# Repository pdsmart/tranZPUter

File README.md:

## Foreword

The tranZPUter is actively being developed and will be reflected in this document.

## Overview

The Sharp MZ80A is based on the Z80 CPU running at 2MHz. It is vintage and under powered compared with modern computers (or a Raspberry Pi). Besides being part of history, it has a software base that is useful from time to time and still has followers. A software Emulator could be written to prolong the usage of the software but there is something special about using original hardware and this is an alternative to keep the machine original yet provide an upgrade that can power the machine with multiple different CPU's (in FPGA, ie. ZPU, 68000 etc) and also power it with a Z80 running upto 128MHz. This is done by bus mastering where the original CPU is tri-stated and the FPGA takes control of the bus.

Besides providing more powerful and alternative CPU's and memory, the FPGA can also act as a Floppy Drive, Hard Drive etc using the connected SD Card and provide a menu system by overlaying the video memory when invoked.

This design is still a work in progress, I stopped development when I needed to advance the ZPU Evo SDRAM controller which I had been putting off for a while. The SDRAM is critical as the Cyclone 10LP on the CYC1000 has limited BRAM, only enough for the cache and IOCP Bootloader. Many features have been tested and the schematic/pcb made, it is just a matter of furthering the VHDL now that the SDRAM controller works and to develop the C/C++ code to provide the menu/SD services (already done in the ZPU code base).

I chose the CYC1000 as the FPGA solution as I am not competent soldering BGA devices, also at US$30 it is quite a cost effective choice. For software minded people, it is not that difficult to use a Pi Zero W or similar in place of the CYC1000 just a reworking of the PCB and interface logic, but that is a project for another time.

As the design replaces a Z80 in-situ it is not limited to the MZ80A but can be used in any Z80 based computer with the right software.

## tranZPUter

The tranZPUter gets its name from: A TRANsformable ZPU compuTER as the base CPU in the FPGA will be the ZPU Evo. The ZPU Evo will provide the Menu, SD, Video Overlay services to the Sharp MZ80A by tri-stating the original Z80 and accessing the MZ80A memory and peripherals as though they were ZPU devices.

To provide different CPU's it is just a matter of mapping in VHDL the softcore CPU signals to the MZ80A bus via this designs interface. The program memory could either be that on the MZ80A or the faster SDRAM. ie. There is no real need to use the MZ80A memory when using a softcore CPU. In my SharpMZ Emulator I run a Z80 at 112MHz using FPGA BRAM but tests show at least 128MHz is sustainable, thus a softcore Z80 CPU running at 128MHz with 48K BRAM slowing down only for MZ80A peripheral access would see a 64x boost in program run, which for say CP/M or database use is very desirable.

In the gallery are pictures of the current design and files uploaded onto github are relatively stable, WIP files wont be uploaded as they are in constant flux.

### Hardware

The basics of this design lie in Z80 bus mastering, ie. the ability to switch the Z80 out of circuit and control the computer as required. Bus mastering was typically used by devices such as DMA for fast transfer of data from an I/O device to memory, or memory to memory 
for applications such as video/graphics. The device taking control of the Z80 bus could transfer data much faster than the Z80 running a program, hence the benefit.

In this design, the bus mastering is used in a similar vein, taking control of the Z80 bus to transfer data between main memory and an SD Card or between the I/O processor and the Video display buffer for presentation of menu's. It is also used where a soft processor
completely idle's the hard Z80 and acts as the main computer CPU. ie. using a soft T-80 ZPU CPU, it can process applications at 128MHz in local memory and slow down to access I/O and the Video buffer on the host machine.

The design centres around lifting the original Z80 onto a daughter card and rerouting several of its signals such that they can be controlled as needed. The core of the design is an FPGA, the Altera Cyclone 10LP on a mini development board made by Trenz Electronics.
This could quite easily be a Raspberry Pi or Teensy 3.6 but the aim of this project is to design electronic hardware in an FPGA using VHDL and making use of the ZPU Processor I have been working on in a seperate project.

The choice of the Trenz Electronic development board put a number of restrictions on the design in so much as it only provides limited I/O facilities. There were not so many other choices of pre-built FPGA development boards with the same size and features to choose from
and designing an FPGA directly into the design from project onset was considered too much a risk because my experience with BGA (Ball Grid Array) packaging and soldering of them was almost zero (I have reballed existing chips but those were working designs!).

As there were limited I/O facilities, I had to make use of two 16bit tri-state buffer latches in an addressed mode rather than a 1:1 mode. ie. The Z80 Data, Address and Control lines eminating out of the FPGA have to be 'set' one word at a time, ie. write data to latch, write address
to latch, write control signals to latch etc. This slows down the speed at which the FPGA can control the Z80 host (to be honest, a 100MHz FPGA can run 50 operations and still match the 2MHz original bus speed) and complicates the logic by requirement of FSM's in VHDL.

It is further complicated by the fact that the signals controlling the latches have themselves to be written in an addressed mode rather than direct, again due to lack of I/O facilities on the FPGA board. Thus in the schematic above you can see IC U6 & U8 being written to via
the common 16bit data bus (shared with the latches) and clocked by a single output signal from the FPGA. A delay line is used such that a write to the latch is performed by signal CYC_CTL/RST going high, this reaches the latch ~8ns after the same signal connected to the Master Reset goes high, thus clocking in the
data. The latches are reset when CYC_CTL/RST goes low and this is enough to control the 16 bit latches U5 & U9. ie. to write a 16bit word into U5 the procedure would be:
```
CYC_CTL/RST low
Set CYC_D0:7 to 0x02 (ADDR_LE active, low)
Set CYC_CTL/RST high, data on CYC_D0:7 is latched into U6/U8 and ADDR_LE goes active enabling transfer of data on CYC_D0:15 into U5 registers (latches on the rising edge of ADDR_LE).
Set required data on CYC_D0:15 that will be passed across to the Z80 BUS.
Set CYC_CTL/RST low, ADDR_LE goes inactive (high) and the data on CYC_D0:15 is latched into U5
```

Once the FPGA FSM is fine tuned, the actual write and read to/from the Z80 bus will be transparent but it is overly complicated as mentioned due to lack of I/O on the Trenz development board. 

### To Do
1. Write the ZPU C/C++ code to take control of the MZ80A, save/update/restore the Video Memory (for Menu system), convert the Main/sharpmz.? Menu/control code, and additional glue to use the SD card.<br/>
2. Convert the T80 CPU to act as a Z80 upgrade for the MZ80A.

## Credits

Where I have used or based any component on a 3rd parties design I have included the original authors copyright notice. All 3rd party software, to my knowledge and research, is open source and freely useable, if there is found to be any component with licensing restrictions, it will be removed from this repository and a suitable link/config provided.

## Licenses

This design, hardware and software, is licensed under the GNU Public Licence v3.

### The Gnu Public License v3
 The source and binary files in this project marked as GPL v3 are free software: you can redistribute it and-or modify it under the terms of the GNU General Public License as published by the Free Software Foundation, either version 3 of the License, or (at your option) any later version.

 The source files are distributed in the hope that it will be useful, but WITHOUT ANY WARRANTY; without even the implied warranty of MERCHANTABILITY or FITNESS FOR A PARTICULAR PURPOSE.  See the GNU General Public License for more details.

 You should have received a copy of the GNU General Public License along with this program.  If not, see http://www.gnu.org/licenses/.

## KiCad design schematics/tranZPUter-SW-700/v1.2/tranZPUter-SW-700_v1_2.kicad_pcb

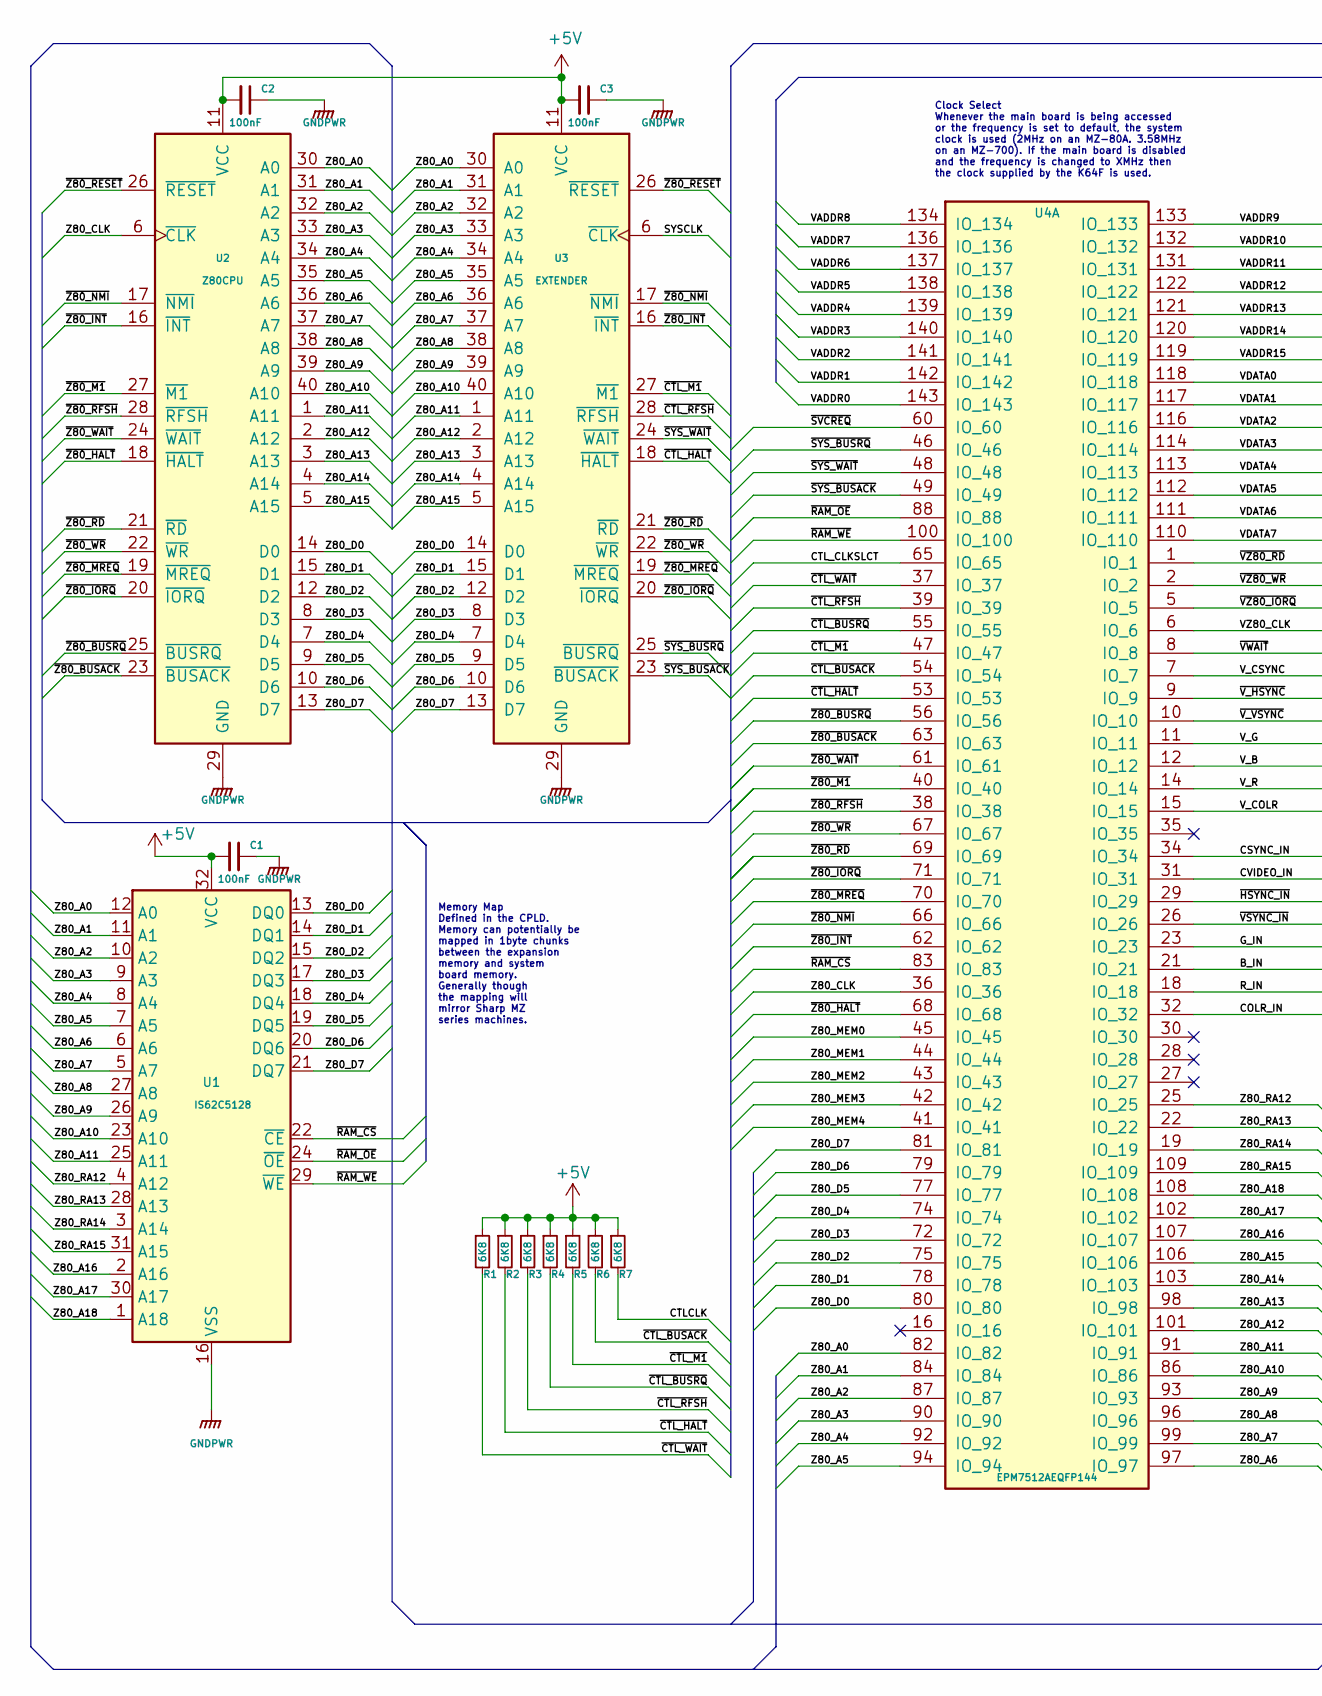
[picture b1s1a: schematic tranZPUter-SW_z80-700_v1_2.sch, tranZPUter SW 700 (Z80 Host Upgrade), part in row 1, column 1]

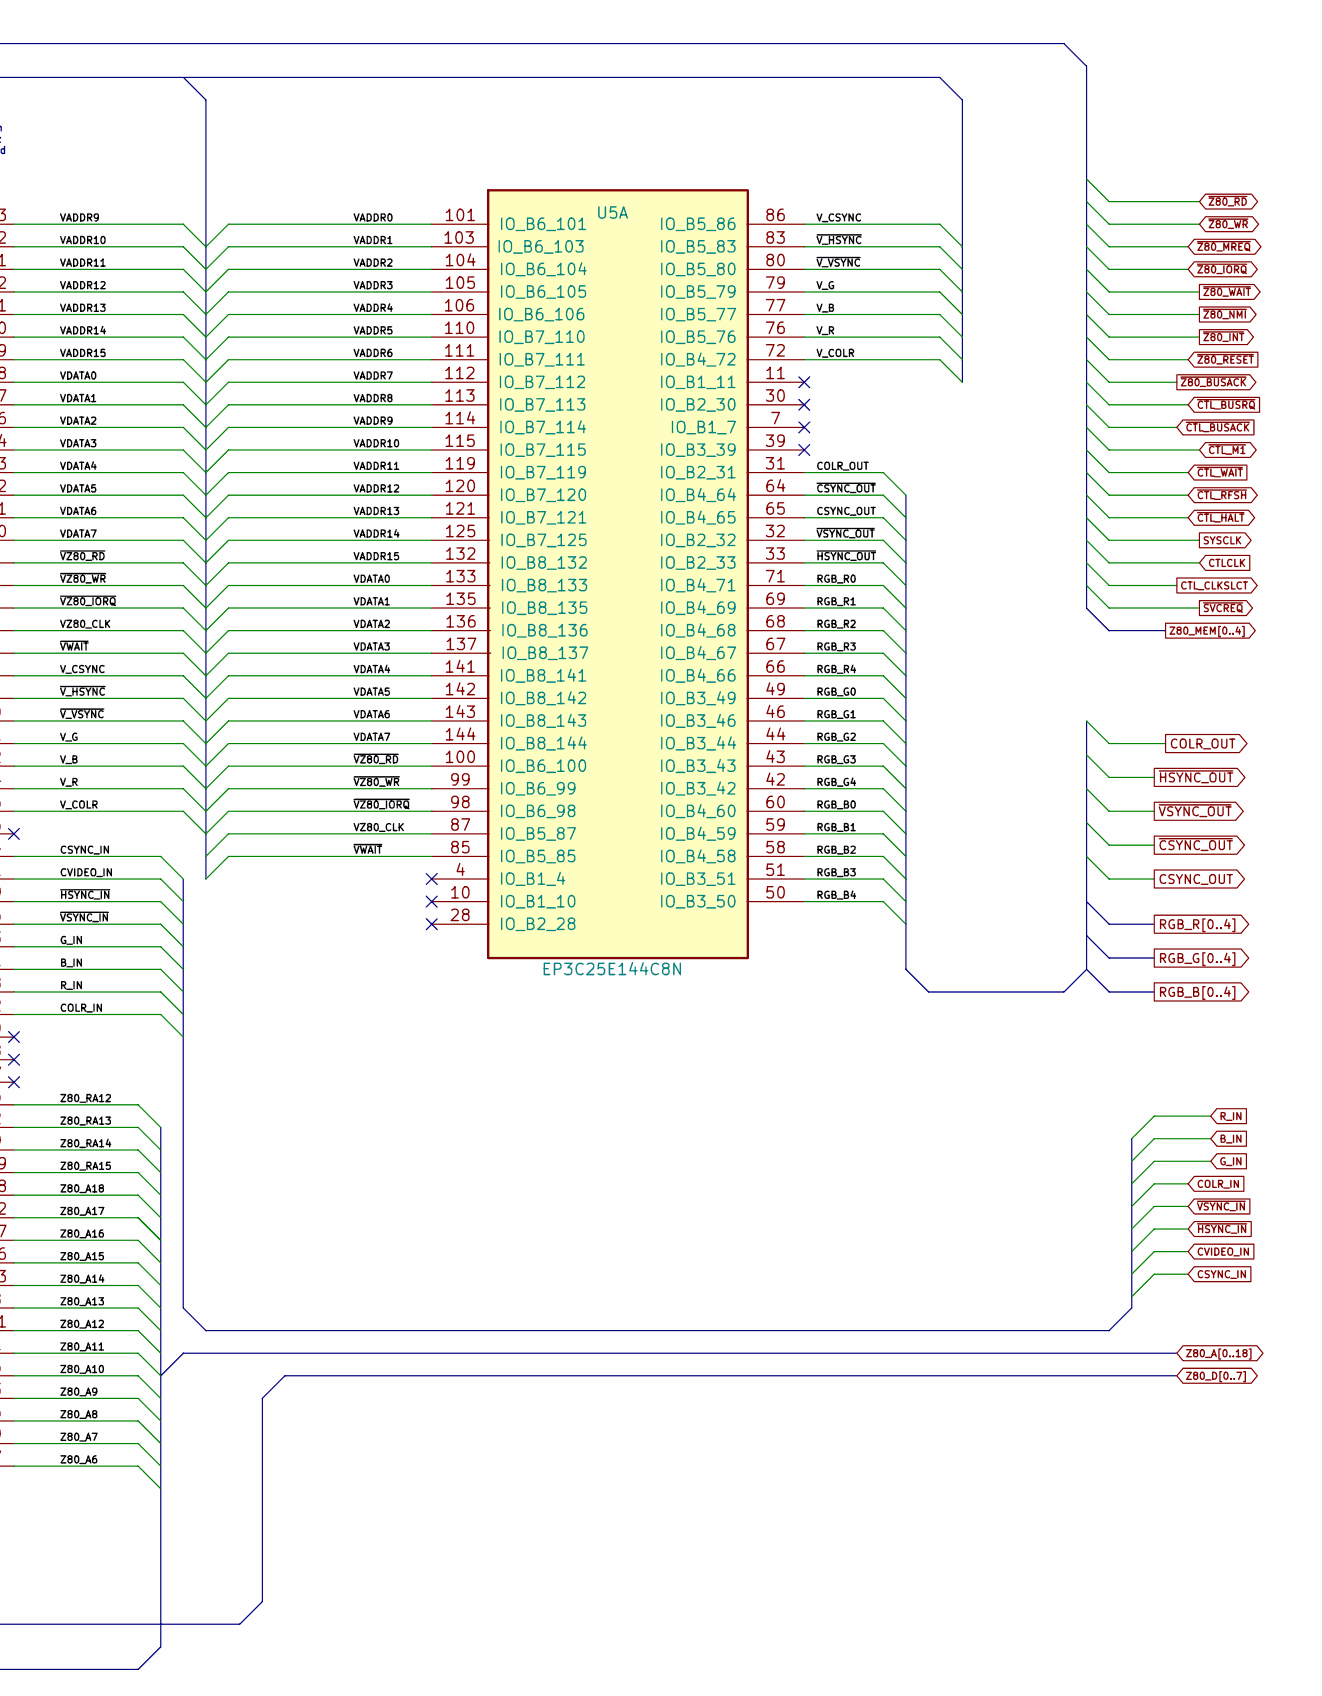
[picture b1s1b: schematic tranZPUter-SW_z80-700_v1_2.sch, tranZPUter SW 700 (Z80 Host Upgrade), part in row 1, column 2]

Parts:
C1, C2, C3: 100nF; C_0805_2012Metric_Pad1.15x1.40mm_HandSolder
R1, R2, R3, R4, R5, R6, R7: 6K8; R_0805_2012Metric_Pad1.15x1.40mm_HandSolder
U1: IS62C5128; TSOP-II-32_21.0x10.2mm_P1.27mm
U2: Z80CPU; DIP-40_W15.24mm_Socket
U3: EXTENDER; DIP-40_W15.24mm_Extender_NoCourtyard
U4: EPM7512AEQFP144; TQFP-144_20x20mm_P0.5mm
U5: EP3C25E144C8N; EQFP-144-1EP_20x20mm_P0.5mm_EP6.61x5.615mm

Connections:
+5V: C1.2, C2.2, C3.2, R1.1, R2.1, R3.1, R4.1, R5.1, R6.1, R7.1, U1.32 (VCC), U2.11 (VCC), U3.11 (VCC); also elsewhere on the board
/Z80 Upgrade/VADDR0: U4.143 (IO_143), U5.101 (IO_B6_101)
/Z80 Upgrade/VADDR1: U4.142 (IO_142), U5.103 (IO_B6_103)
/Z80 Upgrade/VADDR2: U4.141 (IO_141), U5.104 (IO_B6_104)
/Z80 Upgrade/VADDR3: U4.140 (IO_140), U5.105 (IO_B6_105)
/Z80 Upgrade/VADDR4: U4.139 (IO_139), U5.106 (IO_B6_106)
/Z80 Upgrade/VADDR5: U4.138 (IO_138), U5.110 (IO_B7_110)
/Z80 Upgrade/VADDR6: U4.137 (IO_137), U5.111 (IO_B7_111)
/Z80 Upgrade/VADDR7: U4.136 (IO_136), U5.112 (IO_B7_112)
/Z80 Upgrade/VADDR8: U4.134 (IO_134), U5.113 (IO_B7_113)
/Z80 Upgrade/VADDR9: U4.133 (IO_133), U5.114 (IO_B7_114)
/Z80 Upgrade/VADDR10: U4.132 (IO_132), U5.115 (IO_B7_115)
/Z80 Upgrade/VADDR11: U4.131 (IO_131), U5.119 (IO_B7_119)
/Z80 Upgrade/VADDR12: U4.122 (IO_122), U5.120 (IO_B7_120)
/Z80 Upgrade/VADDR13: U4.121 (IO_121), U5.121 (IO_B7_121)
/Z80 Upgrade/VADDR14: U4.120 (IO_120), U5.125 (IO_B7_125)
/Z80 Upgrade/VADDR15: U4.119 (IO_119), U5.132 (IO_B8_132)
/Z80 Upgrade/VDATA0: U4.118 (IO_118), U5.133 (IO_B8_133)
/Z80 Upgrade/VDATA1: U4.117 (IO_117), U5.135 (IO_B8_135)
/Z80 Upgrade/VDATA2: U4.116 (IO_116), U5.136 (IO_B8_136)
/Z80 Upgrade/VDATA3: U4.114 (IO_114), U5.137 (IO_B8_137)
/Z80 Upgrade/VDATA4: U4.113 (IO_113), U5.141 (IO_B8_141)
/Z80 Upgrade/VDATA5: U4.112 (IO_112), U5.142 (IO_B8_142)
/Z80 Upgrade/VDATA6: U4.111 (IO_111), U5.143 (IO_B8_143)
/Z80 Upgrade/VDATA7: U4.110 (IO_110), U5.144 (IO_B8_144)
/Z80 Upgrade/V_B: U4.12 (IO_12), U5.77 (IO_B5_77)
/Z80 Upgrade/V_COLR: U4.15 (IO_15), U5.72 (IO_B4_72)
/Z80 Upgrade/V_CSYNC: U4.7 (IO_7), U5.86 (IO_B5_86)
/Z80 Upgrade/V_CVIDEO: U4.8 (IO_8), U5.85 (IO_B5_85)
/Z80 Upgrade/V_G: U4.11 (IO_11), U5.79 (IO_B5_79)
/Z80 Upgrade/V_R: U4.14 (IO_14), U5.76 (IO_B5_76)
/Z80 Upgrade/Z80_CLK: U2.6 (~CLK~), U4.36 (IO_36)
/Z80 Upgrade/Z80_RA12: U1.4 (A12), U4.25 (IO_25)
/Z80 Upgrade/Z80_RA13: U1.28 (A13), U4.22 (IO_22)
/Z80 Upgrade/Z80_RA14: U1.3 (A14), U4.19 (IO_19)
/Z80 Upgrade/Z80_RA15: U1.31 (A15), U4.109 (IO_109)
/Z80 Upgrade/~RAM_CS~: U1.22 (~CE~), U4.83 (IO_83)
/Z80 Upgrade/~RAM_OE~: U1.24 (~OE~), U4.88 (IO_88)
/Z80 Upgrade/~RAM_WE~: U1.29 (~WE~), U4.100 (IO_100)
/Z80 Upgrade/~SYS_BUSACK~: U3.23 (~BUSACK~), U4.49 (IO_49)
/Z80 Upgrade/~SYS_BUSRQ~: U3.25 (~BUSRQ~), U4.46 (IO_46)
/Z80 Upgrade/~SYS_WAIT~: U3.24 (~WAIT~), U4.48 (IO_48)
/Z80 Upgrade/~VZ80_IORQ~: U4.6 (IO_6), U5.87 (IO_B5_87)
/Z80 Upgrade/~VZ80_MREQ~: U4.5 (IO_5), U5.98 (IO_B6_98)
/Z80 Upgrade/~VZ80_RD~: U4.1 (IO_1), U5.100 (IO_B6_100)
/Z80 Upgrade/~VZ80_WR~: U4.2 (IO_2), U5.99 (IO_B6_99)
/Z80 Upgrade/~V_HSYNC~: U4.9 (IO_9), U5.83 (IO_B5_83)
/Z80 Upgrade/~V_VSYNC~: U4.10 (IO_10), U5.80 (IO_B5_80)
/Z80 Upgrade/~Z80_BUSRQ~: U2.25 (~BUSRQ~), U4.56 (IO_56)
/Z80 Upgrade/~Z80_HALT~: U2.18 (~HALT~), U4.68 (IO_68)
/Z80 Upgrade/~Z80_M1~: U2.27 (~M1~), U4.40 (IO_40)
/Z80 Upgrade/~Z80_RFSH~: U2.28 (~RFSH~), U4.38 (IO_38)
B_IN: U4.21 (IO_21); also elsewhere on the board
COLR_IN: U4.32 (IO_32); also elsewhere on the board
COLR_OUT: U5.31 (IO_B2_31); also elsewhere on the board
CSYNC_IN: U4.34 (IO_34); also elsewhere on the board
CSYNC_OUT: U5.65 (IO_B4_65); also elsewhere on the board
CTLCLK: R7.2; also elsewhere on the board
CTL_CLKSLCT: U4.65 (IO_65); also elsewhere on the board
CVIDEO_IN: U4.31 (IO_31); also elsewhere on the board
GNDPWR: C1.1, C2.1, C3.1, U1.16 (VSS), U2.29 (GND), U3.29 (GND); also elsewhere on the board
G_IN: U4.23 (IO_23); also elsewhere on the board
RGB_B0: U5.60 (IO_B4_60); also elsewhere on the board
RGB_B1: U5.59 (IO_B4_59); also elsewhere on the board
RGB_B2: U5.58 (IO_B4_58); also elsewhere on the board
RGB_B3: U5.51 (IO_B3_51); also elsewhere on the board
RGB_B4: U5.50 (IO_B3_50); also elsewhere on the board
RGB_G0: U5.49 (IO_B3_49); also elsewhere on the board
RGB_G1: U5.46 (IO_B3_46); also elsewhere on the board
RGB_G2: U5.44 (IO_B3_44); also elsewhere on the board
RGB_G3: U5.43 (IO_B3_43); also elsewhere on the board
RGB_G4: U5.42 (IO_B3_42); also elsewhere on the board
RGB_R0: U5.71 (IO_B4_71); also elsewhere on the board
RGB_R1: U5.69 (IO_B4_69); also elsewhere on the board
RGB_R2: U5.68 (IO_B4_68); also elsewhere on the board
RGB_R3: U5.67 (IO_B4_67); also elsewhere on the board
RGB_R4: U5.66 (IO_B4_66); also elsewhere on the board
R_IN: U4.18 (IO_18); also elsewhere on the board
SYSCLK: U3.6 (~CLK~); also elsewhere on the board
Z80_A0: U1.12 (A0), U2.30 (A0), U3.30 (A0), U4.82 (IO_82); also elsewhere on the board
Z80_A1: U1.11 (A1), U2.31 (A1), U3.31 (A1), U4.84 (IO_84); also elsewhere on the board
Z80_A2: U1.10 (A2), U2.32 (A2), U3.32 (A2), U4.87 (IO_87); also elsewhere on the board
Z80_A3: U1.9 (A3), U2.33 (A3), U3.33 (A3), U4.90 (IO_90); also elsewhere on the board
Z80_A4: U1.8 (A4), U2.34 (A4), U3.34 (A4), U4.92 (IO_92); also elsewhere on the board
Z80_A5: U1.7 (A5), U2.35 (A5), U3.35 (A5), U4.94 (IO_94); also elsewhere on the board
Z80_A6: U1.6 (A6), U2.36 (A6), U3.36 (A6), U4.97 (IO_97); also elsewhere on the board
Z80_A7: U1.5 (A7), U2.37 (A7), U3.37 (A7), U4.99 (IO_99); also elsewhere on the board
Z80_A8: U1.27 (A8), U2.38 (A8), U3.38 (A8), U4.96 (IO_96); also elsewhere on the board
Z80_A9: U1.26 (A9), U2.39 (A9), U3.39 (A9), U4.93 (IO_93); also elsewhere on the board
Z80_A10: U1.23 (A10), U2.40 (A10), U3.40 (A10), U4.86 (IO_86); also elsewhere on the board
Z80_A11: U1.25 (A11), U2.1 (A11), U3.1 (A11), U4.91 (IO_91); also elsewhere on the board
Z80_A12: U2.2 (A12), U3.2 (A12), U4.101 (IO_101); also elsewhere on the board
Z80_A13: U2.3 (A13), U3.3 (A13), U4.98 (IO_98); also elsewhere on the board
Z80_A14: U2.4 (A14), U3.4 (A14), U4.103 (IO_103); also elsewhere on the board
Z80_A15: U2.5 (A15), U3.5 (A15), U4.106 (IO_106); also elsewhere on the board
Z80_A16: U1.2 (A16), U4.107 (IO_107); also elsewhere on the board
Z80_A17: U1.30 (A17), U4.102 (IO_102); also elsewhere on the board
Z80_A18: U1.1 (A18), U4.108 (IO_108); also elsewhere on the board
Z80_D0: U1.13 (DQ0), U2.14 (D0), U3.14 (D0), U4.80 (IO_80); also elsewhere on the board
Z80_D1: U1.14 (DQ1), U2.15 (D1), U3.15 (D1), U4.78 (IO_78); also elsewhere on the board
Z80_D2: U1.15 (DQ2), U2.12 (D2), U3.12 (D2), U4.75 (IO_75); also elsewhere on the board
Z80_D3: U1.17 (DQ3), U2.8 (D3), U3.8 (D3), U4.72 (IO_72); also elsewhere on the board
Z80_D4: U1.18 (DQ4), U2.7 (D4), U3.7 (D4), U4.74 (IO_74); also elsewhere on the board
Z80_D5: U1.19 (DQ5), U2.9 (D5), U3.9 (D5), U4.77 (IO_77); also elsewhere on the board
Z80_D6: U1.20 (DQ6), U2.10 (D6), U3.10 (D6), U4.79 (IO_79); also elsewhere on the board
Z80_D7: U1.21 (DQ7), U2.13 (D7), U3.13 (D7), U4.81 (IO_81); also elsewhere on the board
Z80_MEM0: U4.45 (IO_45); also elsewhere on the board
Z80_MEM1: U4.44 (IO_44); also elsewhere on the board
Z80_MEM2: U4.43 (IO_43); also elsewhere on the board
Z80_MEM3: U4.42 (IO_42); also elsewhere on the board
Z80_MEM4: U4.41 (IO_41); also elsewhere on the board
~CSYNC_OUT~: U5.64 (IO_B4_64); also elsewhere on the board
~CTL_BUSACK~: R6.2, U4.54 (IO_54); also elsewhere on the board
~CTL_BUSRQ~: R4.2, U4.55 (IO_55); also elsewhere on the board
~CTL_HALT~: R2.2, U3.18 (~HALT~), U4.53 (IO_53); also elsewhere on the board
~CTL_M1~: R5.2, U3.27 (~M1~), U4.47 (IO_47); also elsewhere on the board
~CTL_RFSH~: R3.2, U3.28 (~RFSH~), U4.39 (IO_39); also elsewhere on the board
~CTL_WAIT~: R1.2, U4.37 (IO_37); also elsewhere on the board
~HSYNC_IN~: U4.29 (IO_29); also elsewhere on the board
~HSYNC_OUT~: U5.33 (IO_B2_33); also elsewhere on the board
~SVCREQ~: U4.60 (IO_60); also elsewhere on the board
~VSYNC_IN~: U4.26 (IO_26); also elsewhere on the board
~VSYNC_OUT~: U5.32 (IO_B2_32); also elsewhere on the board
~Z80_BUSACK~: U2.23 (~BUSACK~), U4.63 (IO_63); also elsewhere on the board
~Z80_INT~: U2.16 (~INT~), U3.16 (~INT~), U4.62 (IO_62); also elsewhere on the board
~Z80_IORQ~: U2.20 (~IORQ~), U3.20 (~IORQ~), U4.71 (IO_71); also elsewhere on the board
~Z80_MREQ~: U2.19 (~MREQ~), U3.19 (~MREQ~), U4.70 (IO_70); also elsewhere on the board
~Z80_NMI~: U2.17 (~NMI~), U3.17 (~NMI~), U4.66 (IO_66); also elsewhere on the board
~Z80_RD~: U2.21 (~RD~), U3.21 (~RD~), U4.69 (IO_69); also elsewhere on the board
~Z80_RESET~: U2.26 (~RESET~), U3.26 (~RESET~); also elsewhere on the board
~Z80_WAIT~: U2.24 (~WAIT~), U4.61 (IO_61); also elsewhere on the board
~Z80_WR~: U2.22 (~WR~), U3.22 (~WR~), U4.67 (IO_67); also elsewhere on the board

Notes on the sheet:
Clock Select Whenever the main board is being accessed or the frequency is set to default, the system clock is used (2MHz on an MZ-80A. 3.58MHz on an MZ-700). If the main board is disabled and the frequency is changed to XMHz then the clock supplied by the K64F is used.
Memory Map Defined in the CPLD. Memory can potentially be mapped in 1byte chunks between the expansion memory and system board memory. Generally though the mapping will mirror Sharp MZ series machines.

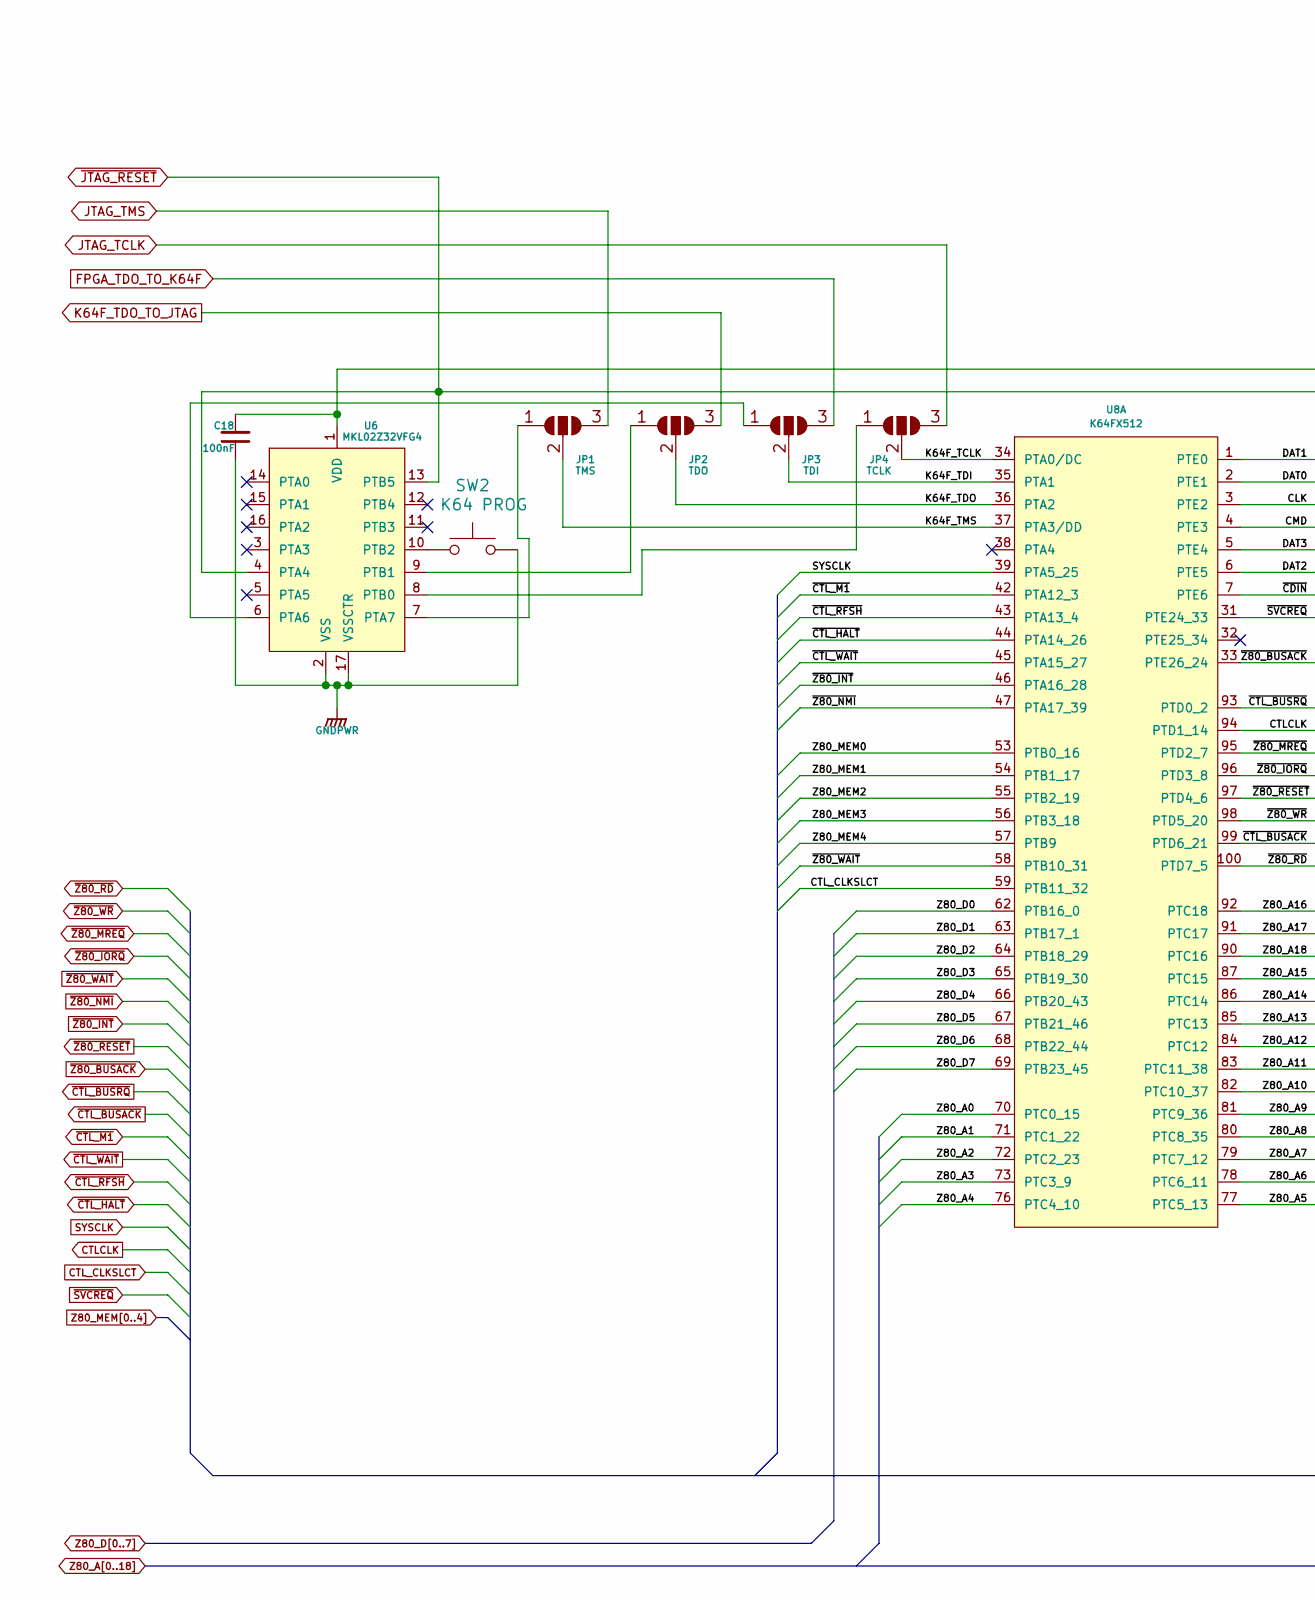
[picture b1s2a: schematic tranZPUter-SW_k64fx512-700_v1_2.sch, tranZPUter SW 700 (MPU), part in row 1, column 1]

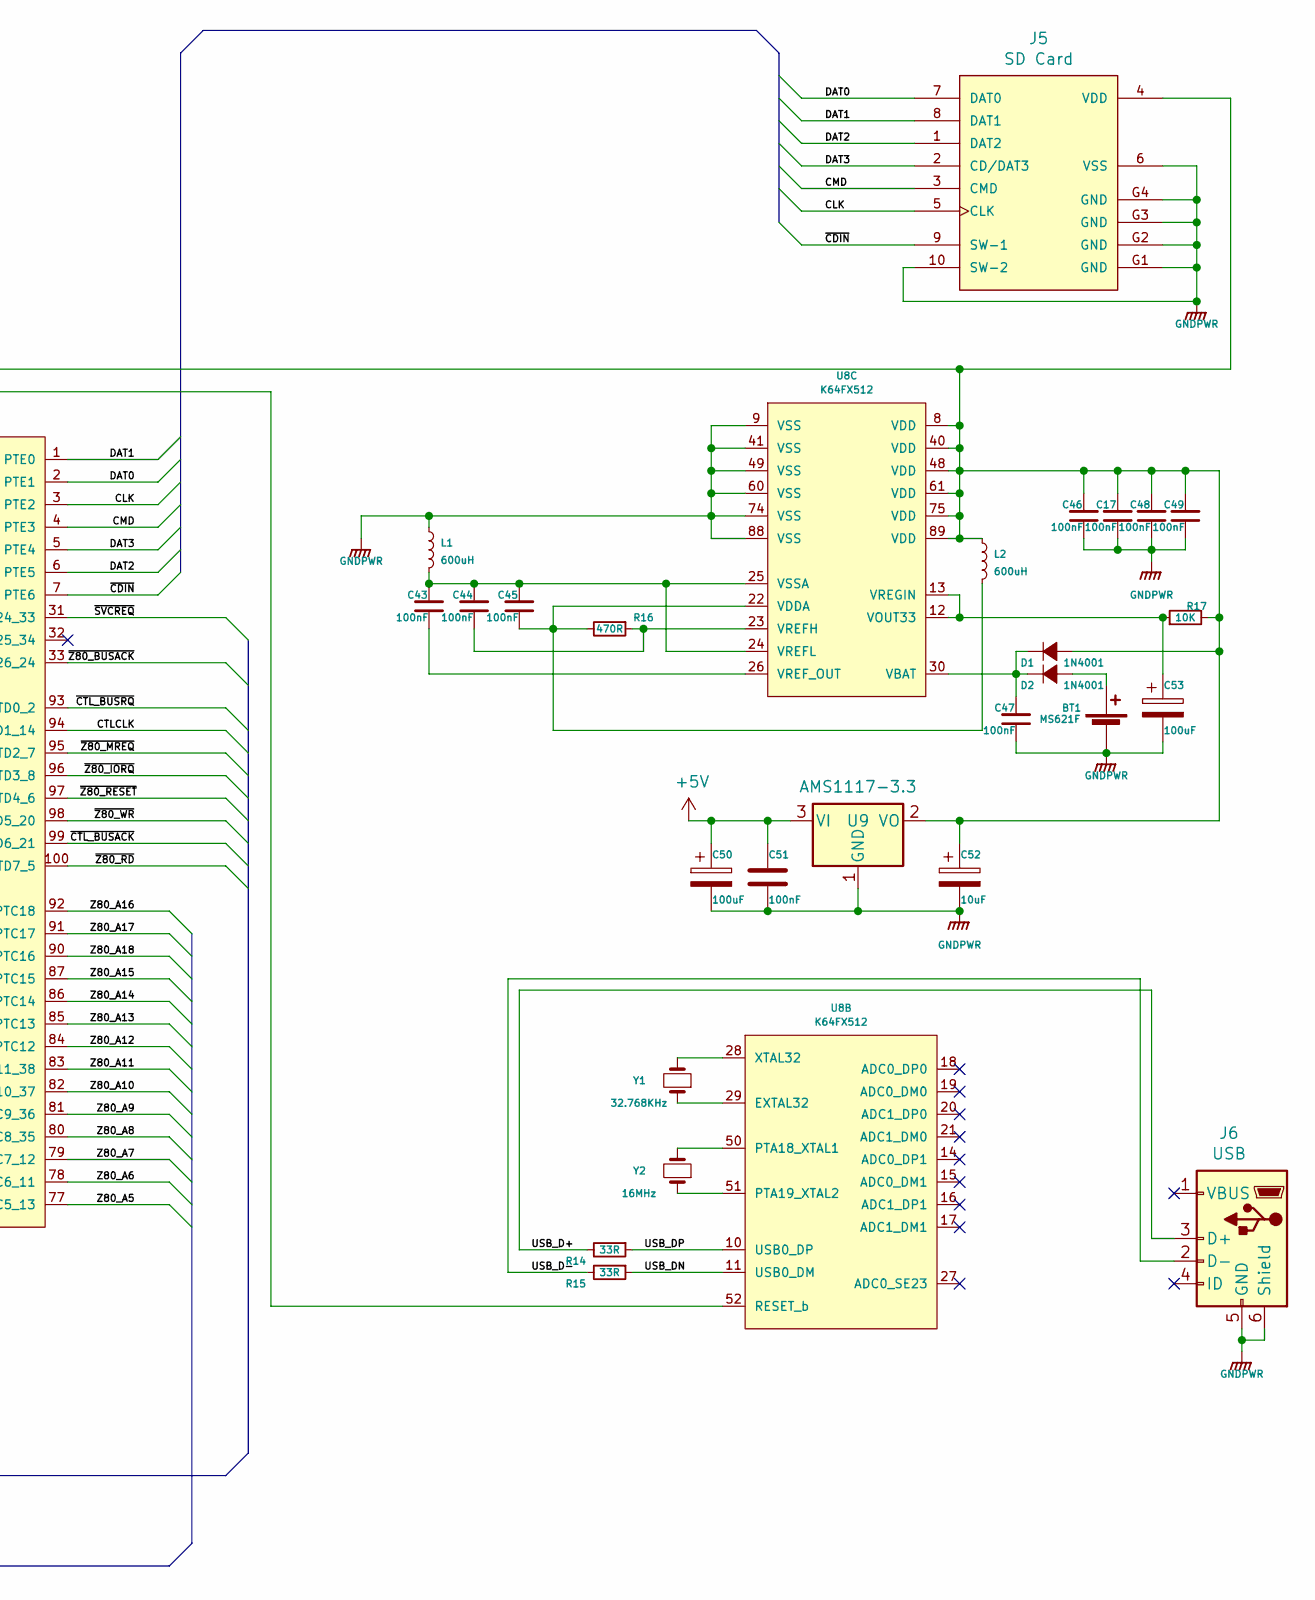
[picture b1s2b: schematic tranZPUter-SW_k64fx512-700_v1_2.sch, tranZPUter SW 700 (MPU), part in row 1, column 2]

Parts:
BT1: MS621F; BatteryHolder_Seiko_MS621F
C17, C18, C43, C44, C45, C46, C47, C48, C49: 100nF; C_0805_2012Metric_Pad1.15x1.40mm_HandSolder
C50, C53: 100uF; C_0603_1608Metric_Pad1.05x0.95mm_HandSolder
C51: 100nF; C_0603_1608Metric_Pad1.05x0.95mm_HandSolder
C52: 10uF; C_0603_1608Metric_Pad1.05x0.95mm_HandSolder
D1, D2: 1N4001; D_1206_3216Metric
J5: SD Card; MOLEX_104031-0811
J6: USB; USB_Micro-B_Amphenol_10103594-0001LF_Horizontal
JP1: TMS; SolderJumper-3_Open
JP2: TDO; SolderJumper-3_Open
JP3: TDI; SolderJumper-3_Open
JP4: TCLK; SolderJumper-3_Open
L1, L2: 600uH; L_0603_1608Metric
R14, R15: 33R; R_0805_2012Metric_Pad1.15x1.40mm_HandSolder
R16: 470R; R_0805_2012Metric_Pad1.15x1.40mm_HandSolder
R17: 10K; R_0805_2012Metric_Pad1.15x1.40mm_HandSolder
SW2: K64 PROG; SW_SPST_B3S-1000
U6: MKL02Z32VFG4; QFN-16-1EP_3x3mm_P0.5mm_EP1.75x1.75mm
U8: K64FX512; LQFP-100_14x14mm_P0.5mm
U9: AMS1117-3.3; SOT-223-3_TabPin2
Y1: 32.768KHz; Crystal_SMD_2012-2Pin_2.0x1.2mm_HandSoldering
Y2: 16MHz; Crystal_SMD_Abracon_ABM8G-4Pin_3.2x2.5mm

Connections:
+5V: C50.1, C51.1, U9.3 (VI); also elsewhere on the board
/NXP K64FX512/CLK: J5.5 (CLK), U8.3 (PTE2)
/NXP K64FX512/CMD: J5.3 (CMD), U8.4 (PTE3)
/NXP K64FX512/DAT0: J5.7 (DAT0), U8.2 (PTE1)
/NXP K64FX512/DAT1: J5.8 (DAT1), U8.1 (PTE0)
/NXP K64FX512/DAT2: J5.1 (DAT2), U8.6 (PTE5)
/NXP K64FX512/DAT3: J5.2 (CD/DAT3), U8.5 (PTE4)
/NXP K64FX512/K64F_TCLK: JP4.2 (C), U8.34 (PTA0/DC)
/NXP K64FX512/K64F_TDI: JP3.2 (C), U8.35 (PTA1)
/NXP K64FX512/K64F_TDO: JP2.2 (C), U8.36 (PTA2)
/NXP K64FX512/K64F_TMS: JP1.2 (C), U8.37 (PTA3/DD)
/NXP K64FX512/USB_D+: J6.3 (D+), R14.2
/NXP K64FX512/USB_D-: J6.2 (D-), R15.2
/NXP K64FX512/USB_DN: R15.1, U8.11 (USB0_DM)
/NXP K64FX512/USB_DP: R14.1, U8.10 (USB0_DP)
/NXP K64FX512/~CDIN~: J5.9 (SW-1), U8.7 (PTE6)
CTLCLK: U8.94 (PTD1_14); also elsewhere on the board
CTL_CLKSLCT: U8.59 (PTB11_32); also elsewhere on the board
FPGA_TDO_TO_K64F: JP3.3 (B); also elsewhere on the board
GNDPWR: BT1.2 (-), C17.1, C18.1, C46.1, C47.1, C48.1, C49.1, C50.2, C51.2, C52.2, C53.2, J5.6 (VSS), J5.10 (SW-2), J5.G1 (GND), J5.G2 (GND), J5.G3 (GND), J5.G4 (GND), J6.5 (GND), J6.6 (Shield), L1.1, SW2.2, U6.2 (VSS), U6.17 (VSSCTR), U8.9 (VSS), U8.41 (VSS), U8.49 (VSS), U8.60 (VSS), U8.74 (VSS), U8.88 (VSS), U9.1 (GND); also elsewhere on the board
JTAG_TCLK: JP4.3 (B); also elsewhere on the board
JTAG_TMS: JP1.3 (B); also elsewhere on the board
K64F_TDO_TO_JTAG: JP2.3 (B); also elsewhere on the board
unnamed: BT1.1 (+), D2.2 (A)
unnamed: C17.2, C18.2, C46.2, C48.2, C49.2, C52.1, D1.2 (A), J5.4 (VDD), L2.1, R17.2, U6.1 (VDD), U8.8 (VDD), U8.40 (VDD), U8.48 (VDD), U8.61 (VDD), U8.75 (VDD), U8.89 (VDD), U9.2 (VO)
unnamed: C43.1, U8.26 (VREF_OUT)
unnamed: C43.2, C44.2, C45.2, L1.2, U8.24 (VREFL), U8.25 (VSSA)
unnamed: C44.1, R16.1, U8.23 (VREFH)
unnamed: C45.1, L2.2, R16.2, U8.22 (VDDA)
unnamed: C47.2, D1.1 (K), D2.1 (K), U8.30 (VBAT)
unnamed: C53.1, R17.1, U8.12 (VOUT33), U8.13 (VREGIN)
unnamed: JP1.1 (A), U6.7 (PTA7)
unnamed: JP2.1 (A), U6.9 (PTB1)
unnamed: JP3.1 (A), U6.6 (PTA6)
unnamed: JP4.1 (A), U6.8 (PTB0)
unnamed: SW2.1, U6.10 (PTB2)
unnamed: U8.28 (XTAL32), Y1.2
unnamed: U8.29 (EXTAL32), Y1.1
unnamed: U8.50 (PTA18_XTAL1), Y2.2
unnamed: U8.51 (PTA19_XTAL2), Y2.1
SYSCLK: U8.39 (PTA5_25); also elsewhere on the board
Z80_A0: U8.70 (PTC0_15); also elsewhere on the board
Z80_A1: U8.71 (PTC1_22); also elsewhere on the board
Z80_A2: U8.72 (PTC2_23); also elsewhere on the board
Z80_A3: U8.73 (PTC3_9); also elsewhere on the board
Z80_A4: U8.76 (PTC4_10); also elsewhere on the board
Z80_A5: U8.77 (PTC5_13); also elsewhere on the board
Z80_A6: U8.78 (PTC6_11); also elsewhere on the board
Z80_A7: U8.79 (PTC7_12); also elsewhere on the board
Z80_A8: U8.80 (PTC8_35); also elsewhere on the board
Z80_A9: U8.81 (PTC9_36); also elsewhere on the board
Z80_A10: U8.82 (PTC10_37); also elsewhere on the board
Z80_A11: U8.83 (PTC11_38); also elsewhere on the board
Z80_A12: U8.84 (PTC12); also elsewhere on the board
Z80_A13: U8.85 (PTC13); also elsewhere on the board
Z80_A14: U8.86 (PTC14); also elsewhere on the board
Z80_A15: U8.87 (PTC15); also elsewhere on the board
Z80_A16: U8.92 (PTC18); also elsewhere on the board
Z80_A17: U8.91 (PTC17); also elsewhere on the board
Z80_A18: U8.90 (PTC16); also elsewhere on the board
Z80_D0: U8.62 (PTB16_0); also elsewhere on the board
Z80_D1: U8.63 (PTB17_1); also elsewhere on the board
Z80_D2: U8.64 (PTB18_29); also elsewhere on the board
Z80_D3: U8.65 (PTB19_30); also elsewhere on the board
Z80_D4: U8.66 (PTB20_43); also elsewhere on the board
Z80_D5: U8.67 (PTB21_46); also elsewhere on the board
Z80_D6: U8.68 (PTB22_44); also elsewhere on the board
Z80_D7: U8.69 (PTB23_45); also elsewhere on the board
Z80_MEM0: U8.53 (PTB0_16); also elsewhere on the board
Z80_MEM1: U8.54 (PTB1_17); also elsewhere on the board
Z80_MEM2: U8.55 (PTB2_19); also elsewhere on the board
Z80_MEM3: U8.56 (PTB3_18); also elsewhere on the board
Z80_MEM4: U8.57 (PTB9); also elsewhere on the board
~CTL_BUSACK~: U8.99 (PTD6_21); also elsewhere on the board
~CTL_BUSRQ~: U8.93 (PTD0_2); also elsewhere on the board
~CTL_HALT~: U8.44 (PTA14_26); also elsewhere on the board
~CTL_M1~: U8.42 (PTA12_3); also elsewhere on the board
~CTL_RFSH~: U8.43 (PTA13_4); also elsewhere on the board
~CTL_WAIT~: U8.45 (PTA15_27); also elsewhere on the board
~JTAG_RESET~: U6.4 (PTA4), U6.13 (PTB5), U8.52 (RESET_b); also elsewhere on the board
~SVCREQ~: U8.31 (PTE24_33); also elsewhere on the board
~Z80_BUSACK~: U8.33 (PTE26_24); also elsewhere on the board
~Z80_INT~: U8.46 (PTA16_28); also elsewhere on the board
~Z80_IORQ~: U8.96 (PTD3_8); also elsewhere on the board
~Z80_MREQ~: U8.95 (PTD2_7); also elsewhere on the board
~Z80_NMI~: U8.47 (PTA17_39); also elsewhere on the board
~Z80_RD~: U8.100 (PTD7_5); also elsewhere on the board
~Z80_RESET~: U8.97 (PTD4_6); also elsewhere on the board
~Z80_WAIT~: U8.58 (PTB10_31); also elsewhere on the board
~Z80_WR~: U8.98 (PTD5_20); also elsewhere on the board
